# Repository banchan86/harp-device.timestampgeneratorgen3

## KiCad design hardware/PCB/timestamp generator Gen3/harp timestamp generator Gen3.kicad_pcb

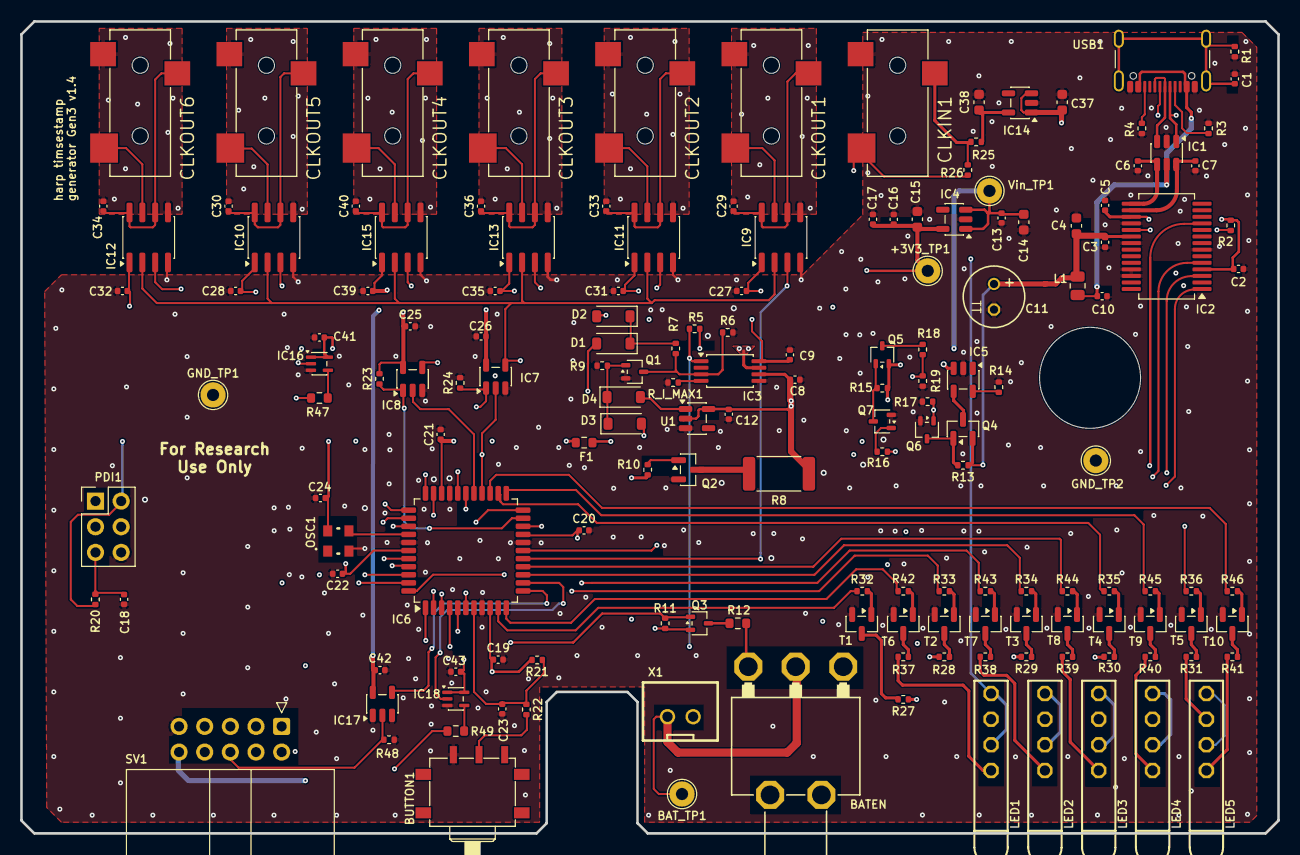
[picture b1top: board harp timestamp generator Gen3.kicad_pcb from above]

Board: 4 copper layers, 124.5 x 80.4 mm, 159 parts (0 on the bottom side), 124 nets.

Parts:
+3V3_TP1: TPPAD1-13; TestPoint_THTPad_D2.5mm_Drill1.2mm
BATEN1: 7101MD9ABE; 2M1-SP1-T2-B4-M6RE
BAT_TP1: TPPAD1-13; TestPoint_THTPad_D2.5mm_Drill1.2mm
BUTTON1: CFPA
C1: 4.7nF; C_0402_1005Metric
C2, C3, C5, C8, C9, C10, C12, C16, C19, C20, C21, C23, C24, C25, C26, C27, C28, C29, C30, C31, C32, C33, C34, C35, C36, C39, C40, C41, C42, C43: 100nF; C_0402_1005Metric
C4, C14, C15, C37, C38: 4.7uF; C_0603_1608Metric
C6, C7: 47pF; C_0402_1005Metric
C11: 100u; TT2D6_334
C13, C17: 10nF; C_0402_1005Metric
C18: 330pF; C_0402_1005Metric
C22: 330nF; C_0402_1005Metric
CLKIN1: 35RASMT2BHNTRX
CLKOUT1, CLKOUT2, CLKOUT3, CLKOUT4, CLKOUT5, CLKOUT6: 35RASMT2BHNTRX
D1, D2, D3, D4: CDBW140-G; D_SOD-123
F1: BLM18SG331TN1D; R_0603_1608Metric
GND_TP1, GND_TP2: TPPAD1-13; TestPoint_THTPad_D2.5mm_Drill1.2mm
IC1: USBLC6-2SC6; SOT-23-6
IC2: FT232RL; SSOP-28_5.3x10.2mm_P0.65mm
IC3: TPS2114; TSSOP-8_4.4x3mm_P0.65mm
IC4, IC14: LP5951MFX-3.3/NOPB; TSOT-23-5
IC5: MCP73831; TSOT-23-5
IC6: ATXMEGA16A4U-A; LQFP-44_10x10mm_P0.8mm
IC7, IC8, IC17: SN74LVC1G125DBVT; SOT-23-5
IC9, IC10, IC11, IC12, IC13, IC15: SI8621BC; SOIC-8_3.9x4.9mm_P1.27mm
IC16, IC18: M74VHC1GT126DF1G; SOT-353_SC-70-5
L1: MI0805K400R-10; R_0805_2012Metric
LED1, LED2, LED3, LED4, LED5: 569-0111-100F; 569-011X-X00_LED_ARRAY
OSC1: ECS-TXO-3225MV-320-TR; OSCILLATOR_3.2X2.5
PDI1: 67996-206HLF; PinHeader_2x03_P2.54mm_Vertical
Q1, Q6: DMG1012UW; SOT-323_SC-70
Q2: SBC817; SOT-23
Q3, Q5: PJC7401_R1_00001; SOT-323_SC-70
Q4: DMP2035U-7; SOT-23
Q7: BC817-40W; SOT-323_SC-70
R1: 1M; R_0402_1005Metric
R2, R7, R15, R20, R22, R23, R24, R26, R48: 10k; R_0402_1005Metric
R3, R4: 5.1k; R_0402_1005Metric
R5, R6: DNP; R_0402_1005Metric
R8: 20R; R_2512_6332Metric
R9, R11, R21: 100k; R_0402_1005Metric
R10, R32, R33, R34, R35, R36, R42, R43, R44, R45, R46: 1k; R_0402_1005Metric
R12, R47, R49: 100R; R_0603_1608Metric
R13, R14, R17: 4.53k; R_0402_1005Metric
R16, R19: 14.7k; R_0402_1005Metric
R18: 51k; R_0402_1005Metric
R25: 10R; R_0402_1005Metric
R27, R28, R29, R30, R31, R37, R38, R39, R40, R41: 330R; R_0402_1005Metric
R_I_MAX1: 1k; R_0402_1005Metric
SV1: SBH11-PBPC-D05-RA-BK; IDC-Header_2x05_P2.54mm_Horizontal
T1, T2, T3, T4, T5, T6, T7, T8, T9, T10: BC850; SOT-23
U1: XC6135C35AMR-G; SOT-23-5
USB1: USB4105-GF-A; USB_C_Receptacle_GCT_USB4105-xx-A_16P_TopMnt_Horizontal
Vin_TP1: TPPAD1-13; TestPoint_THTPad_D2.5mm_Drill1.2mm
X1: B2B-XH-A(LF)(SN); JST-XH-02-PACKAGE-ROUND-PAD

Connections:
+3V3: +3V3_TP1.1 (1_1), C15.1, C16.1, C17.1, C25.1, C26.1, C27.1, C28.1, C31.1, C32.1, C35.1, C39.1, C42.1, F1.2, IC4.5 (OUT), IC7.5 (VCC), IC8.5 (VCC), IC9.1 (AVDD), IC10.1 (AVDD), IC11.1 (AVDD), IC12.1 (AVDD), IC13.1 (AVDD), IC15.1 (AVDD), IC17.5 (VCC), LED1.A1 (A), LED1.A2 (A), LED2.A1 (A), LED2.A2 (A), LED3.A1 (A), LED3.A2 (A), LED4.A1 (A), LED4.A2 (A), LED5.A1 (A), LED5.A2 (A), Q3.2 (S), R11.2, R23.2
+3V3Out: C2.1, C5.1, IC2.4 (VCCIO), IC2.17 (3V3OUT), R2.1
+3V3_u: C19.1, C20.1, C21.1, C22.1, C24.1, F1.1, IC6.9 (VCC@1), IC6.19 (VCC@2), IC6.31 (VCC@3), IC6.39 (AVCC), OSC1.P$4 (VDD), PDI1.2, R20.2, R21.2
+5V_USB: C3.1, C4.1, C9.1, C11.1, D2.2 (A), D3.2 (A), IC2.20 (VCC), IC3.8 (IN1), L1.1, Q4.2 (S), R13.1
+5V_USBIn: C10.1, IC1.5 (VBUS), L1.2, USB1.A4 (VBUS), USB1.A9 (VBUS), USB1.B4 (VBUS), USB1.B9 (VBUS)
/BAT_READ: IC6.41 (PA1/ADC1), R16.1
/BAT_VOLTAGE: IC6.40 (PA0/ADC0/AREF), R18.2, R19.1
/BAT_WAKEUP: IC6.1 (PA5/ADC5), Q3.1 (G), R11.1
/CHARGE_ENABLE: IC6.5 (PB1/ADC9), Q6.1 (G), R17.1
/DISCHARGE_BAT: IC6.6 (PB2/ADC10/DAC0), R10.1
/FTDI_CTS: IC2.11 (CTS), IC6.29 (~XCK0OC0BSCLPE1)
/FTDI_RTS: IC2.3 (RTS), IC6.28 (~OC0ASDAPE0)
/FTDI_RXD: IC2.5 (RXD), IC6.33 (~TXD0OC0DPE3)
/FTDI_TXD: IC2.1 (TXD), IC6.32 (~RXD0OC0CPE2)
/PWR_GOOD: IC3.1 (STAT), IC6.4 (PB0/ADC8/AREF), R5.2
/USBD+: C6.1, IC1.4 (I/O2), IC2.15 (USBD+)
/USBD-: C7.1, IC1.6 (I/O1), IC2.16 (USBD-)
/core/BUTTON: C23.1, IC6.7 (PB3/ADC11/DAC1), R21.1, R22.2
/core/CLOCK_IN: CLKIN1.2, IC6.26 (~RXD1MISOPD6), IC7.2, R26.2
/core/CLOCK_OUT: IC6.27 (~~TXD1SCKCLKOPD7), IC8.2
/core/CLOCK_OUT_ISO: IC7.4, IC8.4, IC9.2 (A1_IN), IC10.2 (A1_IN), IC11.2 (A1_IN), IC12.2 (A1_IN), IC13.2 (A1_IN), IC15.2 (A1_IN), IC16.2
/core/DEVICE_AT_0: IC6.16 (PC6/MISO/RXD1), IC9.3 (A2_OUT)
/core/DEVICE_AT_1: IC6.17 (PC7/SCK/TXD1/CLKO/EVO), IC11.3 (A2_OUT)
/core/DEVICE_AT_2: IC6.44 (PA4/ADC4), IC13.3 (A2_OUT)
/core/DEVICE_AT_3: IC6.36 (PR0/XTAL2), IC15.3 (A2_OUT)
/core/DEVICE_AT_4: IC6.42 (PA2/ADC2), IC10.3 (A2_OUT)
/core/DEVICE_AT_5: IC6.43 (PA3/ADC3), IC12.3 (A2_OUT)
/core/EN_CLOCK_IN: IC6.22 (~OC0CRXD0PD2), IC7.1, R24.1
/core/EN_CLOCK_OUT: IC6.21 (~OC0BXCK0PD1), IC8.1, R23.1
/core/LED_CLK_0: IC6.10 (PC0/OC0A/SDA), R32.1
/core/LED_CLK_1: IC6.3 (PA7/ADC7/AC0-OUT), R33.1
/core/LED_CLK_2: IC6.14 (PC4/OC1A/#SS), R34.1
/core/LED_CLK_3: IC6.11 (PC1/OC0B/XCK0/SCL), R42.2
/core/LED_CLK_4: IC6.2 (PA6/ADC6), R43.1
/core/LED_CLK_5: IC6.15 (PC5/OC1B/MOSI/XCK1), R44.1
/core/LED_LOCK: IC6.24 (~#SSPD4), R35.1
/core/LED_PWR: IC6.20 (~OC0APD0), R36.1
/core/LED_REP: IC6.23 (~OC0DTXD0PD3), R45.1
/core/LEDs & IDC socket/IDC_CLOCK_OUT: R47.1, SV1.2
/core/LEDs & IDC socket/RX: IC17.2, R48.1, SV1.6
/core/LEDs & IDC socket/TX: R49.1, SV1.4
/core/PDI-CLK: C18.1, IC6.35 (RESET/PDI-CLK), PDI1.5, R20.1
/core/PDI-DATA: IC6.34 (PDI-DATA), PDI1.1
/core/STATE: IC6.25 (~XCK1MOSIPD5), R46.1
/core/UC_RX: IC6.12 (PC2/OC0C/RXD0), IC17.4
/core/UC_TX: IC6.13 (PC3/OC0D/TXD0), IC18.2
GND: BUTTON1.1 (A), C1.2, C2.2, C3.2, C4.2, C5.2, C6.2, C7.2, C8.2, C9.2, C10.2, C11.2, C12.2, C13.2, C14.2, C15.2, C16.2, C17.2, C18.2, C19.2, C20.2, C21.2, C22.2, C23.2, C24.2, C25.2, C26.2, C27.2, C28.2, C31.2, C32.2, C35.2, C37.2, C38.2, C39.2, C41.2, C42.2, C43.2, CLKIN1.1, GND_TP1.1 (1_1), GND_TP2.1 (1_1), IC1.2 (GND), IC2.7 (GND), IC2.18 (GND), IC2.21 (GND), IC2.25 (AGND), IC2.26 (TEST), IC3.5 (GND), IC4.2 (GND), IC5.2 (VSS), IC6.8 (GND@1), IC6.18 (GND@2), IC6.30 (GND@3), IC6.38 (GND@4), IC7.3 (GND), IC8.3 (GND), IC9.4 (AGND), IC10.4 (AGND), IC11.4 (AGND), IC12.4 (AGND), IC13.4 (AGND), IC14.2 (GND), IC15.4 (AGND), IC16.3 (GND), IC17.1, IC17.3 (GND), IC18.3 (GND), OSC1.P$2 (GND), PDI1.6, Q1.2 (S), Q2.2 (E), Q6.2 (S), Q7.2 (E), R1.2, R3.2, R4.2, R6.2, R9.1, R14.1, R17.2, R19.2, R24.2, R48.2, R_I_MAX1.2, SV1.9, T1.2 (E), T2.2 (E), T3.2 (E), T4.2 (E), T5.2 (E), T6.2 (E), T7.2 (E), T8.2 (E), T9.2 (E), T10.2 (E), U1.3 (GND), USB1.A1 (GND), USB1.A12 (GND), USB1.B1 (GND), USB1.B12 (GND), X1.2
unnamed: BATEN1.2 (B), BAT_TP1.1 (1_1), X1.1
unnamed: BUTTON1.2 (B), R22.1
unnamed: CLKIN1.3, R25.2, R26.1
unnamed: D1.1 (K), D2.1 (K), R7.2
unnamed: D3.1 (K), D4.1 (K), Q1.1 (G), R9.2
unnamed: D4.2 (A), U1.1 (RESETB)
unnamed: IC1.1 (I/O1), USB1.A7 (D-), USB1.B7 (D-)
unnamed: IC1.3 (I/O2), USB1.A6 (D+), USB1.B6 (D+)
unnamed: IC2.19 (~RESET), R2.2
unnamed: IC3.3 (D1), Q1.3 (D), R6.1, R7.1
unnamed: IC3.4 (ILIM), R_I_MAX1.1
unnamed: IC5.5 (PROG), R14.2
unnamed: IC5.4 (VDD), Q4.3 (D)
unnamed: IC6.37 (PR1/XTAL1), OSC1.P$3 (OUTPUT)
unnamed: CLKOUT1.2, IC9.7 (B1_OUT)
unnamed: C29.1, CLKOUT1.3, IC9.6 (B2_IN), IC9.8 (BVDD)
unnamed: C29.2, CLKOUT1.1, IC9.5 (BGND)
unnamed: CLKOUT5.2, IC10.7 (B1_OUT)
unnamed: C30.1, CLKOUT5.3, IC10.6 (B2_IN), IC10.8 (BVDD)
unnamed: C30.2, CLKOUT5.1, IC10.5 (BGND)
unnamed: CLKOUT2.2, IC11.7 (B1_OUT)
unnamed: C33.1, CLKOUT2.3, IC11.6 (B2_IN), IC11.8 (BVDD)
unnamed: C33.2, CLKOUT2.1, IC11.5 (BGND)
unnamed: CLKOUT6.2, IC12.7 (B1_OUT)
unnamed: C34.1, CLKOUT6.3, IC12.6 (B2_IN), IC12.8 (BVDD)
unnamed: C34.2, CLKOUT6.1, IC12.5 (BGND)
unnamed: CLKOUT3.2, IC13.7 (B1_OUT)
unnamed: C36.1, CLKOUT3.3, IC13.6 (B2_IN), IC13.8 (BVDD)
unnamed: C36.2, CLKOUT3.1, IC13.5 (BGND)
unnamed: C38.1, IC14.5 (OUT), R25.1
unnamed: CLKOUT4.2, IC15.7 (B1_OUT)
unnamed: C40.1, CLKOUT4.3, IC15.6 (B2_IN), IC15.8 (BVDD)
unnamed: C40.2, CLKOUT4.1, IC15.5 (BGND)
unnamed: IC16.4, R47.2
unnamed: IC18.4, R49.2
unnamed: LED1.C1 (C), R37.1
unnamed: LED1.C2 (C), R27.1
unnamed: LED2.C1 (C), R38.1
unnamed: LED2.C2 (C), R28.1
unnamed: LED3.C1 (C), R39.1
unnamed: LED3.C2 (C), R29.1
unnamed: LED4.C1 (C), R40.1
unnamed: LED4.C2 (C), R30.1
unnamed: LED5.C1 (C), R41.1
unnamed: LED5.C2 (C), R31.1
unnamed: Q2.1 (B), R10.2
unnamed: Q2.3 (C), R8.2
unnamed: Q3.3 (D), R12.2
unnamed: Q4.1 (G), Q6.3 (D), R13.2
unnamed: Q5.3 (D), R18.1
unnamed: Q5.1 (G), Q7.3 (C), R15.1
unnamed: Q7.1 (B), R16.2
unnamed: R32.2, T1.1 (B)
unnamed: R27.2, T1.3 (C)
unnamed: R33.2, T2.1 (B)
unnamed: R28.2, T2.3 (C)
unnamed: R34.2, T3.1 (B)
unnamed: R29.2, T3.3 (C)
unnamed: R35.2, T4.1 (B)
unnamed: R30.2, T4.3 (C)
unnamed: R36.2, T5.1 (B)
unnamed: R31.2, T5.3 (C)
unnamed: R42.1, T6.1 (B)
unnamed: R37.2, T6.3 (C)
unnamed: R43.2, T7.1 (B)
unnamed: R38.2, T7.3 (C)
unnamed: R44.2, T8.1 (B)
unnamed: R39.2, T8.3 (C)
unnamed: R45.2, T9.1 (B)
unnamed: R40.2, T9.3 (C)
unnamed: R46.2, T10.1 (B)
unnamed: R41.2, T10.3 (C)
unnamed: R3.1, USB1.A5 (CC1)
unnamed: R4.1, USB1.B5 (CC2)
unnamed: C1.1, R1.1, USB1.SH (SHIELD)
VBatt: BATEN1.1 (A), C8.1, C12.1, D1.2 (A), IC3.6 (IN2), IC5.3 (VBAT), Q5.2 (S), R8.1, R12.1, R15.2, U1.2 (Vin), U1.5 (Vsens)
Vin: C13.1, C14.1, C37.1, C41.1, C43.1, IC3.7 (OUT), IC4.1 (IN), IC4.3 (EN), IC14.1 (IN), IC14.3 (EN), IC16.1, IC16.5 (VCC), IC18.1, IC18.5 (VCC), R5.1, SV1.10, Vin_TP1.1 (1_1)

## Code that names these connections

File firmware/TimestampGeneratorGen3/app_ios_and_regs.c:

#include <avr/io.h>
#include "hwbp_core_types.h"
#include "app_ios_and_regs.h"

extern AppRegs app_regs;

/************************************************************************/
/* Configure and initialize IOs                                         */
/************************************************************************/
void init_ios(void)
{
    /* Configure input pins */
    io_pin2in(&PORTA, 2, PULL_IO_TRISTATE, SENSE_IO_NO_INT_USED);        // DEVICE_AT_4
    io_pin2in(&PORTA, 3, PULL_IO_TRISTATE, SENSE_IO_NO_INT_USED);        // DEVICE_AT_5
    io_pin2in(&PORTA, 4, PULL_IO_TRISTATE, SENSE_IO_NO_INT_USED);        // DEVICE_AT_2
    io_pin2in(&PORTB, 0, PULL_IO_UP, SENSE_IO_EDGES_BOTH);               // POWER_GOOD
    io_pin2in(&PORTB, 3, PULL_IO_TRISTATE, SENSE_IO_EDGES_BOTH);         // BUTTON
    io_pin2in(&PORTC, 6, PULL_IO_TRISTATE, SENSE_IO_NO_INT_USED);        // DEVICE_AT_0
    io_pin2in(&PORTC, 7, PULL_IO_TRISTATE, SENSE_IO_NO_INT_USED);        // DEVICE_AT_1
    io_pin2in(&PORTR, 0, PULL_IO_TRISTATE, SENSE_IO_NO_INT_USED);        // DEVICE_AT_3

    /* Configure input interrupts */
    io_set_int(&PORTB, INT_LEVEL_LOW, 0, (1<<0), false);                 // POWER_GOOD

    /* Configure output pins */
    io_pin2out(&PORTA, 1, OUT_IO_DIGITAL, IN_EN_IO_EN);                  // BAT_READ
    io_pin2out(&PORTA, 5, OUT_IO_DIGITAL, IN_EN_IO_EN);                  // EN_SCREEN_BACKLIGHT
    io_pin2out(&PORTA, 6, OUT_IO_DIGITAL, IN_EN_IO_EN);                  // LED_CLK_4
    io_pin2out(&PORTA, 7, OUT_IO_DIGITAL, IN_EN_IO_EN);                  // LED_CLK_1
    io_pin2out(&PORTB, 1, OUT_IO_DIGITAL, IN_EN_IO_EN);                  // EN_CHARGE
    io_pin2out(&PORTB, 2, OUT_IO_DIGITAL, IN_EN_IO_EN);                  // EN_DISCHARGE
    io_pin2out(&PORTC, 0, OUT_IO_DIGITAL, IN_EN_IO_EN);                  // LED_CLK_0
    io_pin2out(&PORTC, 1, OUT_IO_DIGITAL, IN_EN_IO_EN);                  // LED_CLK_3
    io_pin2out(&PORTC, 4, OUT_IO_DIGITAL, IN_EN_IO_EN);                  // LED_CLK_2
    io_pin2out(&PORTC, 5, OUT_IO_DIGITAL, IN_EN_IO_EN);                  // LED_CLK_5
    io_pin2out(&PORTD, 0, OUT_IO_DIGITAL, IN_EN_IO_EN);                  // LED_POWER
    io_pin2out(&PORTD, 1, OUT_IO_DIGITAL, IN_EN_IO_EN);                  // EN_CLOCK_OUT
    io_pin2out(&PORTD, 2, OUT_IO_DIGITAL, IN_EN_IO_EN);                  // EN_CLOCK_IN
    io_pin2out(&PORTD, 3, OUT_IO_DIGITAL, IN_EN_IO_EN);                  // LED_REPEATER
    io_pin2out(&PORTD, 4, OUT_IO_DIGITAL, IN_EN_IO_EN);                  // LED_LOCK
    io_pin2out(&PORTD, 5, OUT_IO_DIGITAL, IN_EN_IO_EN);                  // LED_STATE

    /* Initialize output pins */
    clr_BAT_READ;
    clr_EN_SCREEN_BACKLIGHT;
    clr_LED_CLK_4;
    clr_LED_CLK_1;
    clr_EN_CHARGE;
    clr_EN_DISCHARGE;
    clr_LED_CLK_0;
    clr_LED_CLK_3;
    clr_LED_CLK_2;
    clr_LED_CLK_5;
    clr_LED_POWER;
    clr_EN_CLOCK_OUT;
    set_EN_CLOCK_IN;
    clr_LED_REPEATER;
    clr_LED_LOCK;
    clr_LED_STATE;
}

/************************************************************************/
/* Registers' stuff                                                     */
/************************************************************************/
AppRegs app_regs;

uint8_t app_regs_type[] = {
    TYPE_U8,
    TYPE_U8,
    TYPE_U8,
    TYPE_U8,
    TYPE_FLOAT,
    TYPE_FLOAT,
    TYPE_FLOAT,
    TYPE_U16,
    TYPE_U16,
    TYPE_U32,
    TYPE_U8
};

uint16_t app_regs_n_elements[] = {
    1,
    1,
    1,
    1,
    1,
    1,
    1,
    1,
    1,
    1,
    1
};

uint8_t *app_regs_pointer[] = {
    (uint8_t*)(&app_regs.REG_CONFIG),
    (uint8_t*)(&app_regs.REG_DEVICES_CONNECTED),
    (uint8_t*)(&app_regs.REG_REPEATER_STATUS),
    (uint8_t*)(&app_regs.REG_BATTERY_RATE),
    (uint8_t*)(&app_regs.REG_BATTERY),
    (uint8_t*)(&app_regs.REG_BATTERY_THRESHOLD_LOW),
    (uint8_t*)(&app_regs.REG_BATTERY_THRESHOLD_HIGH),
    (uint8_t*)(&app_regs.REG_BATTERY_CALIBRATION0),
    (uint8_t*)(&app_regs.REG_BATTERY_CALIBRATION1),
    (uint8_t*)(&app_regs.REG_TIMER),
    (uint8_t*)(&app_regs.REG_TIMER_FREQUENCY)
};

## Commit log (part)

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2026-06-22 Scaffold minimal docfx website
2026-06-22 Regenerate interface to pass build step check
2026-06-22 Allow unsafe blocks in newly generated interface
2026-06-22 Fix package output path
2026-06-22 Add gitattributes
2026-06-22 Temp remove GH actions to fix broken pipeline
2026-06-22 Add back GH actions recipe
2026-06-23 Add GitHub actions recipe
